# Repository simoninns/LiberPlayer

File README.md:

# LiberPlayer
LiberPlayer is a LaserDisc video player emulator designed as part of the Domesday86 project.

This project is beta and highly experimental - you won't find anything useful in this repository at the moment unless you are directly involved in the project's development.

For more detail of the Domesday86 project please see https://www.domesday86.com

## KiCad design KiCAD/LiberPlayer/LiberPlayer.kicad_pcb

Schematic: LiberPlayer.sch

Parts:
JP101: GPIO_0; IDC-Header_2x20_P2.54mm_Vertical
R101, R102: 2K2; R_0805_2012Metric

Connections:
+3V3: JP101.29, R101.1, R102.1; also elsewhere on the board
+5V: JP101.11; also elsewhere on the board
GND: JP101.12, JP101.30; also elsewhere on the board
I2C_SCL: JP101.1, R101.2; also elsewhere on the board
I2C_SDA: JP101.2, R102.2; also elsewhere on the board
PC_SCK: JP101.18; also elsewhere on the board
PC_SIn: JP101.21; also elsewhere on the board
PC_SOut: JP101.20; also elsewhere on the board
PC_~CS: JP101.19; also elsewhere on the board
VideoD_DCLK: JP101.15; also elsewhere on the board
VideoD_FSS: JP101.16; also elsewhere on the board
VideoD_Y0: JP101.3; also elsewhere on the board
VideoD_Y1: JP101.4; also elsewhere on the board
VideoD_Y2: JP101.5; also elsewhere on the board
VideoD_Y3: JP101.6; also elsewhere on the board
VideoD_Y4: JP101.7; also elsewhere on the board
VideoD_Y5: JP101.8; also elsewhere on the board
VideoD_Y6: JP101.9; also elsewhere on the board
VideoD_Y7: JP101.10; also elsewhere on the board
VideoD_Y8: JP101.13; also elsewhere on the board
VideoD_Y9: JP101.14; also elsewhere on the board
VideoD_~RESET: JP101.17; also elsewhere on the board

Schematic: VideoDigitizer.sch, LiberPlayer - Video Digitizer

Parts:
C201, C202, C203, C204, C205, C206, C207, C208, C209, C210, C211, C214, C215, C216, C217, C218, C219, C220, C221, C222, C223, C224, C225: 100nF; C_0805_2012Metric
C212, C213: 33pF; C_0805_2012Metric
R201, R202: 10K; R_0805_2012Metric
R203, R204: 2K2; R_0805_2012Metric
TP201: INTREQ; TestPoint_Pad_1.0x1.0mm
U201: TVP5146; TQFP-80_12x12mm_P0.5mm
Y201: 14.31818 MHz; Crystal_SMD_0603-2Pin_6.0x3.5mm

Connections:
+1V8D: C201.1, C202.1, C203.1, C204.1, C205.1, C207.1, C209.1, C211.1, C214.1, C216.1, U201.11, U201.12, U201.14, U201.25, U201.31, U201.41, U201.55, U201.67, U201.76, U201.78; also elsewhere on the board
+3V3D: C218.1, C220.1, C221.1, C222.1, C223.1, C224.1, C225.1, R202.2, U201.4, U201.5, U201.20, U201.21, U201.38, U201.48, U201.61; also elsewhere on the board
/Power Supply/~RESET: U201.34; also elsewhere on the board
/Video Digitizer/RGB_Blue: U201.80; also elsewhere on the board
/Video Digitizer/RGB_Green: U201.7; also elsewhere on the board
/Video Digitizer/RGB_Red: U201.16; also elsewhere on the board
/Video Front-End/CVBS_Sync: U201.23; also elsewhere on the board
GND: C201.2, C202.2, C203.2, C204.2, C205.2, C206.2, C207.2, C208.2, C209.2, C210.2, C211.2, C212.2, C213.2, C214.2, C215.2, C216.2, C217.2, C218.2, C219.2, C220.2, C221.2, C222.2, C223.2, C224.2, C225.2, R201.2, R203.1, R204.1, U201.3, U201.6, U201.10, U201.13, U201.15, U201.19, U201.22, U201.24, U201.26, U201.27, U201.32, U201.39, U201.42, U201.49, U201.56, U201.62, U201.68, U201.77, U201.79; also elsewhere on the board
I2C_SCL: U201.28; also elsewhere on the board
I2C_SDA: U201.29; also elsewhere on the board
unnamed: C206.1, U201.1
unnamed: C208.1, U201.2
unnamed: C210.1, U201.8
unnamed: C215.1, U201.9
unnamed: C217.1, U201.17
unnamed: C219.1, U201.18
unnamed: R201.1, U201.33
unnamed: R202.1, U201.37
unnamed: R203.2, U201.71
unnamed: R204.2, U201.69
unnamed: TP201.1, U201.30
VideoD_DCLK: U201.40; also elsewhere on the board
VideoD_FSS: U201.35; also elsewhere on the board
VideoD_Y0: U201.54; also elsewhere on the board
VideoD_Y1: U201.53; also elsewhere on the board
VideoD_Y2: U201.52; also elsewhere on the board
VideoD_Y3: U201.51; also elsewhere on the board
VideoD_Y4: U201.50; also elsewhere on the board
VideoD_Y5: U201.47; also elsewhere on the board
VideoD_Y6: U201.46; also elsewhere on the board
VideoD_Y7: U201.45; also elsewhere on the board
VideoD_Y8: U201.44; also elsewhere on the board
VideoD_Y9: U201.43; also elsewhere on the board
XTAL1: C212.1, U201.74, Y201.1
XTAL2: C213.1, U201.75, Y201.2

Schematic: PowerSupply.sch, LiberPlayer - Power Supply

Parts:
C301: 47uF Tant; CP_EIA-7343-31_Kemet-D
C302, C303: 100nF; C_0805_2012Metric
C304, C305: 10uF Tant; CP_EIA-7343-31_Kemet-D
R301: 249K; R_0805_2012Metric
U301: TPS70151PWP; TSSOP-20_4.4x6.5mm_P0.65mm

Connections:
+1V8D: C305.1, U301.12, U301.13, U301.14; also elsewhere on the board
+3V3D: C304.1, R301.1, U301.17, U301.18, U301.19; also elsewhere on the board
+5V: C301.1, C302.2, C303.2, U301.2, U301.3, U301.9, U301.10; also elsewhere on the board
/Power Supply/~RESET: R301.2, U301.15; also elsewhere on the board
GND: C301.2, C302.1, C303.1, C304.2, C305.2, U301.7, U301.8; also elsewhere on the board
unnamed: U301.4, U301.16
VideoD_~RESET: U301.6; also elsewhere on the board

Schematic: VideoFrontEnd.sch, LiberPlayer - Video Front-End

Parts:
C401, C402, C403, C404, C409, C410, C411, C412: 330pF; C_0805_2012Metric
C405, C406, C407, C408: 680pF; C_0805_2012Metric
C413, C414, C415, C416: 100nF; C_0805_2012Metric
J401: BBC Master RGB; 6P DIN Socket RS Pro
J402: CVBS in; PinHeader_1x02_P2.54mm_Vertical
L401, L402, L403, L404, L405, L406, L407, L408: 2.7uH; L_0805_2012Metric
R401, R402, R403: 220R; R_0805_2012Metric
R404: 270R; R_0805_2012Metric
R405, R406, R407, R408: 75R; R_0805_2012Metric

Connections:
/Video Digitizer/RGB_Blue: C415.1; also elsewhere on the board
/Video Digitizer/RGB_Green: C414.1; also elsewhere on the board
/Video Digitizer/RGB_Red: C413.1; also elsewhere on the board
/Video Front-End/CVBS_Sync: C416.1; also elsewhere on the board
GND: C401.2, C402.2, C403.2, C404.2, C405.2, C406.2, C407.2, C408.2, C409.2, C410.2, C411.2, C412.2, J401.5, J401.7, J401.8, J402.2, R405.1, R406.1, R407.1, R408.1; also elsewhere on the board
unnamed: C401.1, L401.2, R401.2
unnamed: C402.1, L402.2, R402.2
unnamed: C403.1, L403.2, R403.2
unnamed: C404.1, J402.1, L404.2, R404.2
unnamed: C405.1, L401.1, L405.2
unnamed: C406.1, L402.1, L406.2
unnamed: C407.1, L403.1, L407.2
unnamed: C408.1, L404.1, L408.2
unnamed: C409.1, C413.2, L405.1, R405.2
unnamed: C410.1, C414.2, L406.1, R406.2
unnamed: C411.1, C415.2, L407.1, R407.2
unnamed: C412.1, C416.2, L408.1, R408.2
unnamed: J401.1, R401.1
unnamed: J401.2, R402.1
unnamed: J401.3, R403.1
unnamed: J401.4, R404.1

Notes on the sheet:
Red
Green
Blue
CVBS/Sync

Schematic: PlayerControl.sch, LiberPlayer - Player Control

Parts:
C501, C502: 100nF; C_0805_2012Metric
R501: 10K; R_0805_2012Metric
U501, U502: MCP23S17; SSOP-28_5.3x10.2mm_P0.65mm

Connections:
+3V3: C501.1, C502.1, R501.1, U501.9, U502.9, U502.15; also elsewhere on the board
/Player Control/RS232C Interface/RS232_CTS: U502.4; also elsewhere on the board
/Player Control/RS232C Interface/RS232_DTR: U502.2; also elsewhere on the board
/Player Control/RS232C Interface/RS232_RxD: U502.3; also elsewhere on the board
/Player Control/RS232C Interface/RS232_TxD: U502.1; also elsewhere on the board
/Player Control/SCSI-1 Interface/~ACK: U501.24; also elsewhere on the board
/Player Control/SCSI-1 Interface/~ATN: U501.22; also elsewhere on the board
/Player Control/SCSI-1 Interface/~BSY: U501.23; also elsewhere on the board
/Player Control/SCSI-1 Interface/~C~D: U501.28; also elsewhere on the board
/Player Control/SCSI-1 Interface/~DB0: U501.1; also elsewhere on the board
/Player Control/SCSI-1 Interface/~DB1: U501.2; also elsewhere on the board
/Player Control/SCSI-1 Interface/~DB2: U501.3; also elsewhere on the board
/Player Control/SCSI-1 Interface/~DB3: U501.4; also elsewhere on the board
/Player Control/SCSI-1 Interface/~DB4: U501.5; also elsewhere on the board
/Player Control/SCSI-1 Interface/~DB5: U501.6; also elsewhere on the board
/Player Control/SCSI-1 Interface/~DB6: U501.7; also elsewhere on the board
/Player Control/SCSI-1 Interface/~DB7: U501.8; also elsewhere on the board
/Player Control/SCSI-1 Interface/~I~O: U502.22; also elsewhere on the board
/Player Control/SCSI-1 Interface/~MSG: U501.26; also elsewhere on the board
/Player Control/SCSI-1 Interface/~PARITY: U501.21; also elsewhere on the board
/Player Control/SCSI-1 Interface/~REQ: U502.21; also elsewhere on the board
/Player Control/SCSI-1 Interface/~RST: U501.25; also elsewhere on the board
/Player Control/SCSI-1 Interface/~SEL: U501.27; also elsewhere on the board
GND: C501.2, C502.2, U501.10, U501.15, U501.16, U501.17, U502.10, U502.16, U502.17; also elsewhere on the board
unnamed: R501.2, U501.18, U502.18
unnamed: U501.14, U502.13
PC_SCK: U501.12, U502.12; also elsewhere on the board
PC_SIn: U501.13; also elsewhere on the board
PC_SOut: U502.14; also elsewhere on the board
PC_~CS: U501.11, U502.11; also elsewhere on the board

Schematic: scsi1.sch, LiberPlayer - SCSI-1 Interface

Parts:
J601: SCSI-1 IDC; IDC-Header_2x25_P2.54mm_Vertical
RN601, RN603: 220R; R_Array_SIP10
RN602, RN604: 330R; R_Array_SIP10

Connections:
+5V: RN601.1, RN603.1; also elsewhere on the board
/Player Control/SCSI-1 Interface/~ACK: J601.38, RN603.4, RN604.8; also elsewhere on the board
/Player Control/SCSI-1 Interface/~ATN: J601.32, RN603.2, RN604.10; also elsewhere on the board
/Player Control/SCSI-1 Interface/~BSY: J601.36, RN603.3, RN604.9; also elsewhere on the board
/Player Control/SCSI-1 Interface/~C~D: J601.46, RN603.8, RN604.4; also elsewhere on the board
/Player Control/SCSI-1 Interface/~DB0: J601.2, RN601.2, RN602.10; also elsewhere on the board
/Player Control/SCSI-1 Interface/~DB1: J601.4, RN601.3, RN602.9; also elsewhere on the board
/Player Control/SCSI-1 Interface/~DB2: J601.6, RN601.4, RN602.8; also elsewhere on the board
/Player Control/SCSI-1 Interface/~DB3: J601.8, RN601.5, RN602.7; also elsewhere on the board
/Player Control/SCSI-1 Interface/~DB4: J601.10, RN601.6, RN602.6; also elsewhere on the board
/Player Control/SCSI-1 Interface/~DB5: J601.12, RN601.7, RN602.5; also elsewhere on the board
/Player Control/SCSI-1 Interface/~DB6: J601.14, RN601.8, RN602.4; also elsewhere on the board
/Player Control/SCSI-1 Interface/~DB7: J601.16, RN601.9, RN602.3; also elsewhere on the board
/Player Control/SCSI-1 Interface/~I~O: J601.50, RN603.10, RN604.2; also elsewhere on the board
/Player Control/SCSI-1 Interface/~MSG: J601.42, RN603.6, RN604.6; also elsewhere on the board
/Player Control/SCSI-1 Interface/~PARITY: J601.18, RN601.10, RN602.2; also elsewhere on the board
/Player Control/SCSI-1 Interface/~REQ: J601.48, RN603.9, RN604.3; also elsewhere on the board
/Player Control/SCSI-1 Interface/~RST: J601.40, RN603.5, RN604.7; also elsewhere on the board
/Player Control/SCSI-1 Interface/~SEL: J601.44, RN603.7, RN604.5; also elsewhere on the board
GND: J601.1, J601.3, J601.5, J601.7, J601.9, J601.11, J601.13, J601.15, J601.17, J601.19, J601.20, J601.21, J601.22, J601.23, J601.24, J601.25, J601.27, J601.28, J601.29, J601.30, J601.31, J601.33, J601.35, J601.37, J601.39, J601.41, J601.43, J601.45, J601.47, J601.49, RN602.1, RN604.1; also elsewhere on the board

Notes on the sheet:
Note: On early Acorn SCSI implementations pin 34 was connected to 5V (when it should be GND according to SCSI-1). So here is it left NC.

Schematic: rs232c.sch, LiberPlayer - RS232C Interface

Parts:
C701, C702, C703, C704, C705: 100nF; C_0805_2012Metric
J701: RS232C DCE; DSUB-25_Female_Horizontal_P2.77x2.84mm_EdgePinOffset7.70mm_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
U701: MAX3232IDRG4; SOIC-16_3.9x9.9mm_P1.27mm

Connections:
+3V3: C705.1, U701.16 (VCC); also elsewhere on the board
/Player Control/RS232C Interface/RS232_CTS: U701.7 (T2OUT); also elsewhere on the board
/Player Control/RS232C Interface/RS232_DTR: U701.8 (R2IN); also elsewhere on the board
/Player Control/RS232C Interface/RS232_RxD: U701.14 (T1OUT); also elsewhere on the board
/Player Control/RS232C Interface/RS232_TxD: U701.13 (R1IN); also elsewhere on the board
CTS: J701.5, U701.10 (T2IN)
DTR: J701.20, U701.9 (R2OUT)
GND: C703.2, C704.1, C705.2, J701.0, J701.7, U701.15 (GND); also elsewhere on the board
unnamed: C701.1, U701.1 (C1+)
unnamed: C701.2, U701.3 (C1-)
unnamed: C702.1, U701.4 (C2+)
unnamed: C702.2, U701.5 (C2-)
unnamed: C703.1, U701.6 (VS-)
unnamed: C704.2, U701.2 (VS+)
RxD: J701.3, U701.11 (T1IN)
TxD: J701.2, U701.12 (R1OUT)

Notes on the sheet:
VP415 RS232 pin-out: 2 (TxD) transmitted data from player to computer 3 (RxD) received data from computer to player 5 (CTS) clear to send: a signal from computer to player indicating the computer is ready to receive data (+3V means ok to transmit) 7 (GND) logic ground 9 +12V/100 mA 10 -12V/10 mA 20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

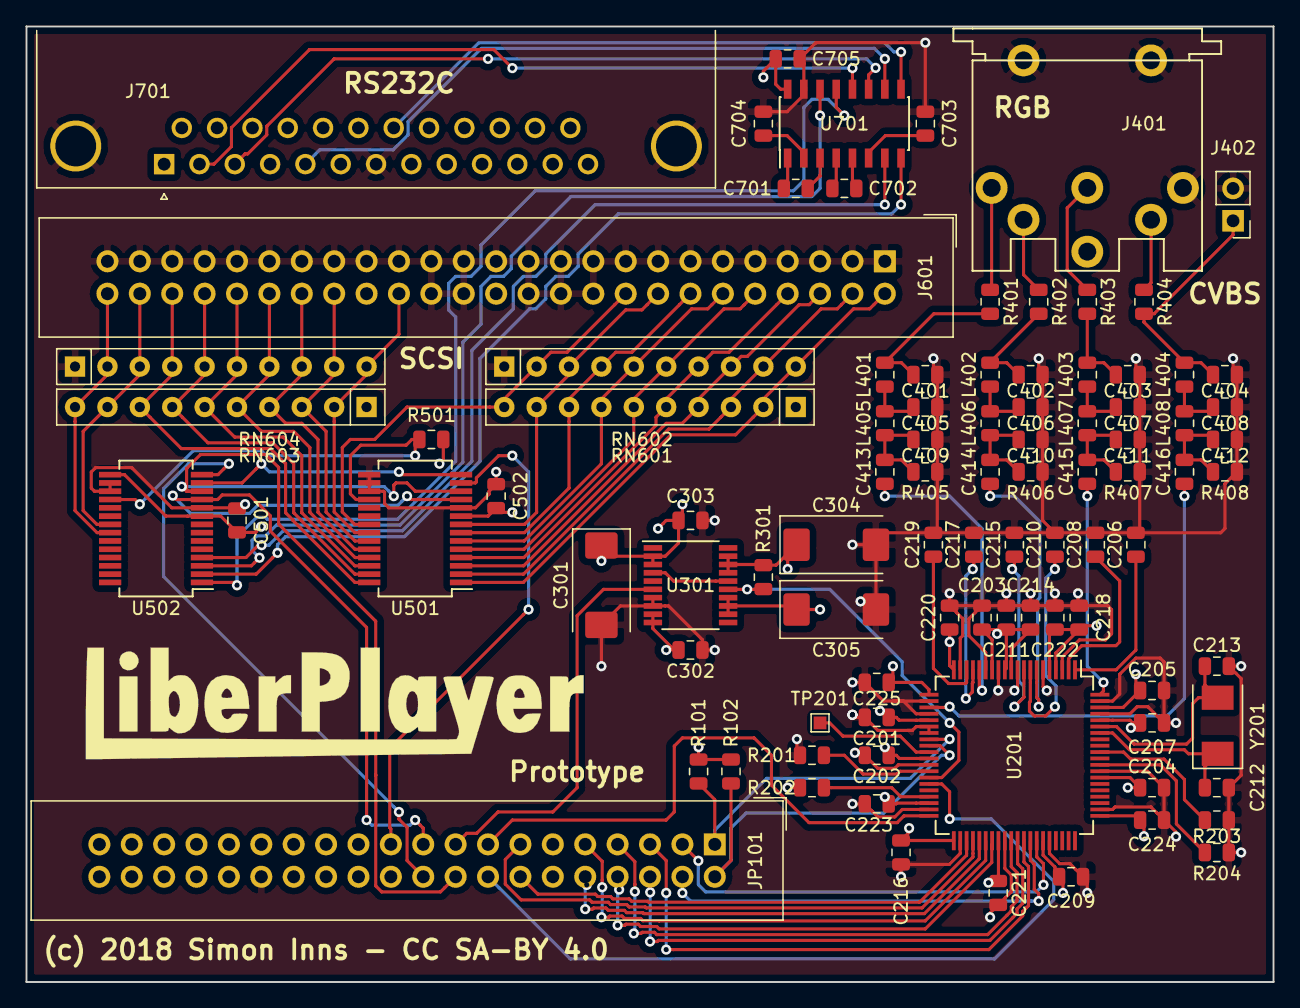
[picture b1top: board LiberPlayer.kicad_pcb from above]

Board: 4 copper layers, 97.8 x 74.9 mm, 93 parts (0 on the bottom side), 93 nets.

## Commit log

2018-10-05 High level design documentation drafts and logo
2018-10-05 Initial sketch of video digitizer design
2018-10-05 Added video front end and filters
2018-10-05 Added RS232 interface
2018-10-05 Added KiCAD gitignore and cleaned up files
2018-10-06 Added GPIO and ADC header library for DE10-Nano
2018-10-06 File clean-up after merge
2018-10-06 Added power supply and test points to design
2018-10-06 Added SCSI-1 interface, power supply fixes and DE10-Nano interconnection
2018-10-06 ERC error corrections
2018-10-07 Added RGB socket symbol and footprint - first pass at allocating all footprints
2018-10-07 Foot-print assignments and initial PCB creation
2018-10-08 Added I2C front-end to player control (serial and SCSI)
2018-10-08 Revised schematic (SPI to SCSI) and board design (incomplete)
2018-10-08 Added logo to PCB
2018-10-09 Finised PCB and added all required support files

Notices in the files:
KiCAD/LiberPlayer/LiberPlayer.kicad_pcb:
(c) 2018 Simon Inns
License: Attribution-ShareAlike 4.0 International (CC BY-SA 4.0)
(c) 2018 Simon Inns - CC SA-BY 4.0
